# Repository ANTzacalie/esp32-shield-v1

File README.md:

# ESP32 Shield V1

---

## About the Project

- Shield V1 is spacious development shield designed to make working with ESP32 reliable, practical, and accessible. Whether you're prototyping, learning, or building something more permanent, this board gives you the room and connectivity to do it right.

The ESP32 Shield V1 breaks out **all useful GPIO pins** (bootstrapping pins like GPIO11 excluded) through both **terminal block connectors** for permanent wiring and **male pin headers** for Dupont jumper wire access. It supports both the **ESP32 DevKit C** and **ESP32-S** variants — both fit into the onboard 2×19 socket pins.

Power is supplied through a modern **USB-C 6-pin connector**, compatible with any USB-C charger or USB-A to USB-C adapter — no more bulky legacy connectors. A **power LED** confirms the board is live at a glance.

---

## Features

    -  **USB-C Power Input** — 6-pin USB-C connector; works with any USB-C or USB-A (female-to-USB-C) charger
    -  **Full GPIO Breakout** — all useful ESP32 GPIO pins exposed (bootstrapping pins excluded)
    -  **Terminal Block Connectors** — for all useful pins, ideal for permanent or semi-permanent wiring
    -  **Male Pin Headers** — Dupont-compatible, for quick breadboard or jumper wire access
    -  **ESP32 DevKit C & 32S Compatible** — both modules fit the 2×19 socket pin layout
    -  **5V Rail up to 1A** — 2 terminal blocks with 5V and GND in 1:1 configuration
    -  **5V & 3.3V Header Pins** — 2×4 header for 5V and 3.3V (max 500mA via AMS1117-3.3 regulator)
    -  **4×4 GND Header** — dedicated ground header block
    -  **Power Indicator LED** — shows board is powered and ready
    -  **Big, Spacious Board** — generous layout for comfortable hand soldering and clear wiring

---

## Gallery

<p align="center">
  
  &nbsp;&nbsp;
  
</p>

---

## Documents

| Document | Link |
|---|---|
| PCB Layout | [shield_v1_pcb.pdf](esp32_development_shield_v1/auxiliar/screenshots/shield_v1_pcb.pdf) |
| Schematic | [shield_v1_schematic.pdf](esp32_development_shield_v1/auxiliar/screenshots/shield_v1_schematic.pdf) |

---

## Demo

https://github.com/user-attachments/assets/38adf7bb-4b09-42fa-a934-d43c7a3f349f

---

## Folder Structure

```
esp32-shield-v1/
│
├── auxiliar/
│   ├── compatibility_info/       # Compatibility notes for ESP32 variants
│   ├── screenshots/              # Board photos (photo1–photo4)
│   └── test_video/               # Demo video (video.gif / video.mp4)
│
├── pcb/
│   ├── bom_files/                # 📋 Bill of Materials (BOM)
│   ├── drill_files/              # 🔩 Drill files for PCB fabrication
│   └── gerber_files/             # 📦 Gerber files — send these to your PCB fab
│
└── schematic/
    ├── esp32_node_devkit_shield_v1/   # Main schematic project files
    └── symbols&footprints/            # Custom KiCad symbols and footprints
```

> **PCB fabrication files are located in `/pcb/`:**
> - **`/pcb/gerber_files/`** — Production-ready Gerber files for your PCB manufacturer
> - **`/pcb/drill_files/`** — Drill/Excellon files for hole placement
> - **`/pcb/bom_files/`** — Bill of Materials for component sourcing

---

## Getting Started

1. Clone or download this repository
2. Open the schematic in **KiCad** from `/schematic/esp32_node_devkit_shield_v1/`
3. Review the BOM in `/pcb/bom_files/` and source your components
4. Send the files from `/pcb/gerber_files/` and `/pcb/drill_files/` to your preferred PCB manufacturer
5. Assemble, plug in your ESP32 DevKit C or 32S, connect USB-C power, and build something!

---

## Compatibility

| Module | Fits? |
|---|---|
| ESP32 DevKit C | ✅ Yes |
| ESP32-S (DevKitS) | ✅ Yes |

See `/auxiliar/compatibility_info/` for detailed notes.

---

## Power Specifications

| Rail | Max Current | Connector Type |
|---|---|---|
| 5V | 1A | 2× Terminal Block (5V + GND) |
| 5V | — | 2×4 Pin Header |
| 3.3V | 500mA | 2×4 Pin Header (AMS1117-3.3) |
| GND | — | 4×4 Pin Header |

---

## License

This project is open source. Feel free to use, modify, and build upon it for personal and educational purposes.

---

*Made with monster-energy and a soldering iron — student electronics project*

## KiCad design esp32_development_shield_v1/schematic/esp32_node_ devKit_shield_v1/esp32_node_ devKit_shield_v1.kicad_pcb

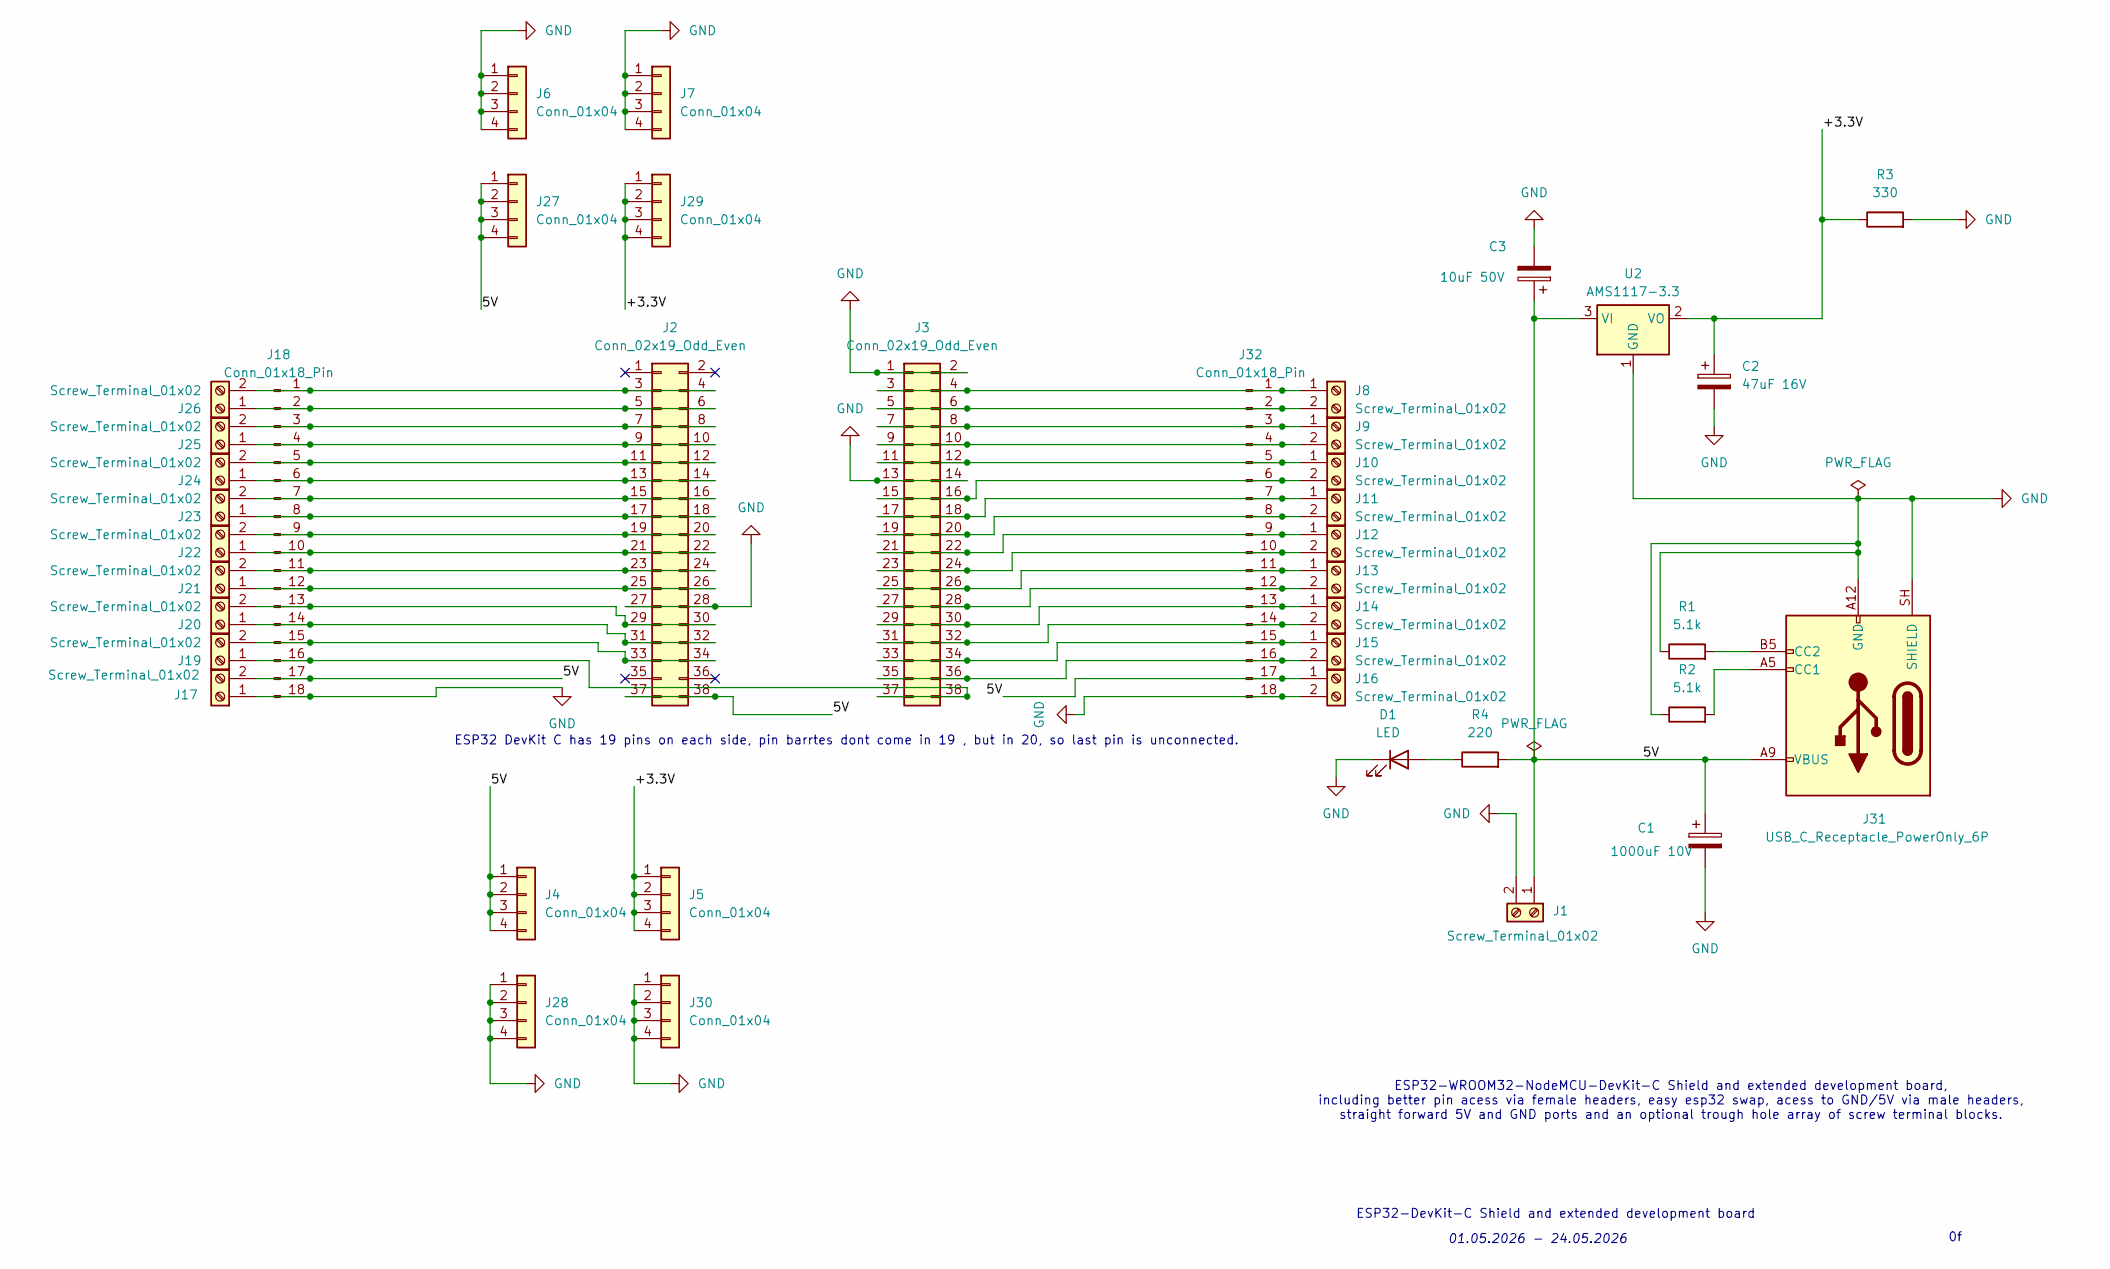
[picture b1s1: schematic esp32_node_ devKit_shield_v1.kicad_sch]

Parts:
C1: 1000uF 10V; CP_Radial_D10.0mm_P5.00mm
C2: 47uF 16V; CP_Radial_D8.0mm_P5.00mm
C3: 10uF 50V; CP_Radial_D8.0mm_P5.00mm
D1: LED; LED_Rectangular_W3.0mm_H2.0mm
J1, J8, J9, J10, J11, J12, J13, J14, J15, J16, J17, J19, J20, J21, J22, J23, J24, J25, J26: Screw_Terminal_01x02; TerminalBlock_RND_205-00232_1x02_P5.08mm_Horizontal
J2, J3: Conn_02x19_Odd_Even; PinSocket_2x19_P2.54mm_Vertical
J4, J5, J6, J7, J27, J28, J29, J30: Conn_01x04; PinHeader_1x04_P2.54mm_Vertical
J18, J32: Conn_01x18_Pin; PinHeader_1x18_P2.54mm_Vertical
J31: USB_C_Receptacle_PowerOnly_6P; USB_C_Receptacle_GCT_USB4125-xx-x_6P_TopMnt_Horizontal
R1, R2: 5.1k; R_Axial_DIN0207_L6.3mm_D2.5mm_P10.16mm_Horizontal
R3: 330; R_Axial_DIN0207_L6.3mm_D2.5mm_P10.16mm_Horizontal
R4: 220; R_Axial_DIN0207_L6.3mm_D2.5mm_P10.16mm_Horizontal
U2: AMS1117-3.3; SOT-223-3_TabPin2

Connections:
/5V: C1.1, C3.1, J1.1, J2.37, J2.38, J4.1, J4.2, J4.3, J4.4, J16.1, J17.2, J18.17, J27.1, J27.2, J27.3, J27.4, J31.A9 (VBUS), J31.B9 (VBUS), J32.17, R4.2, U2.3 (VI)
/+3.3V: C2.1, J5.1, J5.2, J5.3, J5.4, J29.1, J29.2, J29.3, J29.4, R3.1, U2.2 (VO)
GND: C1.2, C2.2, C3.2, D1.1 (K), J1.2, J2.27, J2.28, J3.1, J3.2, J3.13, J3.14, J6.1, J6.2, J6.3, J6.4, J7.1, J7.2, J7.3, J7.4, J16.2, J17.1, J18.18, J28.1, J28.2, J28.3, J28.4, J30.1, J30.2, J30.3, J30.4, J31.A12 (GND), J31.B12 (GND), J31.SH (SHIELD), J32.18, R1.1, R2.1, R3.2, U2.1 (GND)
unnamed: D1.2 (A), R4.1
unnamed: J3.3, J3.4, J8.1, J32.1
unnamed: J3.5, J3.6, J8.2, J32.2
unnamed: J3.7, J3.8, J9.1, J32.3
unnamed: J3.9, J3.10, J9.2, J32.4
unnamed: J3.11, J3.12, J10.1, J32.5
unnamed: J3.15, J3.16, J10.2, J32.6
unnamed: J3.17, J3.18, J11.1, J32.7
unnamed: J3.19, J3.20, J11.2, J32.8
unnamed: J3.21, J3.22, J12.1, J32.9
unnamed: J3.23, J3.24, J12.2, J32.10
unnamed: J3.25, J3.26, J13.1, J32.11
unnamed: J3.27, J3.28, J13.2, J32.12
unnamed: J3.29, J3.30, J14.1, J32.13
unnamed: J3.31, J3.32, J14.2, J32.14
unnamed: J3.33, J3.34, J15.1, J32.15
unnamed: J3.35, J3.36, J15.2, J32.16
unnamed: J2.3, J2.4, J18.1, J26.2
unnamed: J2.5, J2.6, J18.2, J26.1
unnamed: J2.7, J2.8, J18.3, J25.2
unnamed: J2.9, J2.10, J18.4, J25.1
unnamed: J2.11, J2.12, J18.5, J24.2
unnamed: J2.13, J2.14, J18.6, J24.1
unnamed: J2.15, J2.16, J18.7, J23.2
unnamed: J2.17, J2.18, J18.8, J23.1
unnamed: J2.19, J2.20, J18.9, J22.2
unnamed: J2.21, J2.22, J18.10, J22.1
unnamed: J2.23, J2.24, J18.11, J21.2
unnamed: J2.25, J2.26, J18.12, J21.1
unnamed: J2.29, J2.30, J18.13, J20.2
unnamed: J2.31, J2.32, J18.14, J20.1
unnamed: J2.33, J2.34, J18.15, J19.2
unnamed: J3.37, J3.38, J18.16, J19.1
unnamed: J31.A5 (CC1), R2.2
unnamed: J31.B5 (CC2), R1.2

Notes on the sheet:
ESP32-DevKit-C Shield and extended development board
ESP32-WROOM32-NodeMCU-DevKit-C Shield and extended development board, including better pin acess via female headers, easy esp32 swap, acess to GND/5V via male headers, straight forward 5V and GND ports and an optional trough hole array of screw terminal blocks.
ESP32 DevKit C has 19 pins on each side, pin barrtes dont come in 19 , but in 20, so last pin is unconnected.
01.05.2026 - 24.05.2026

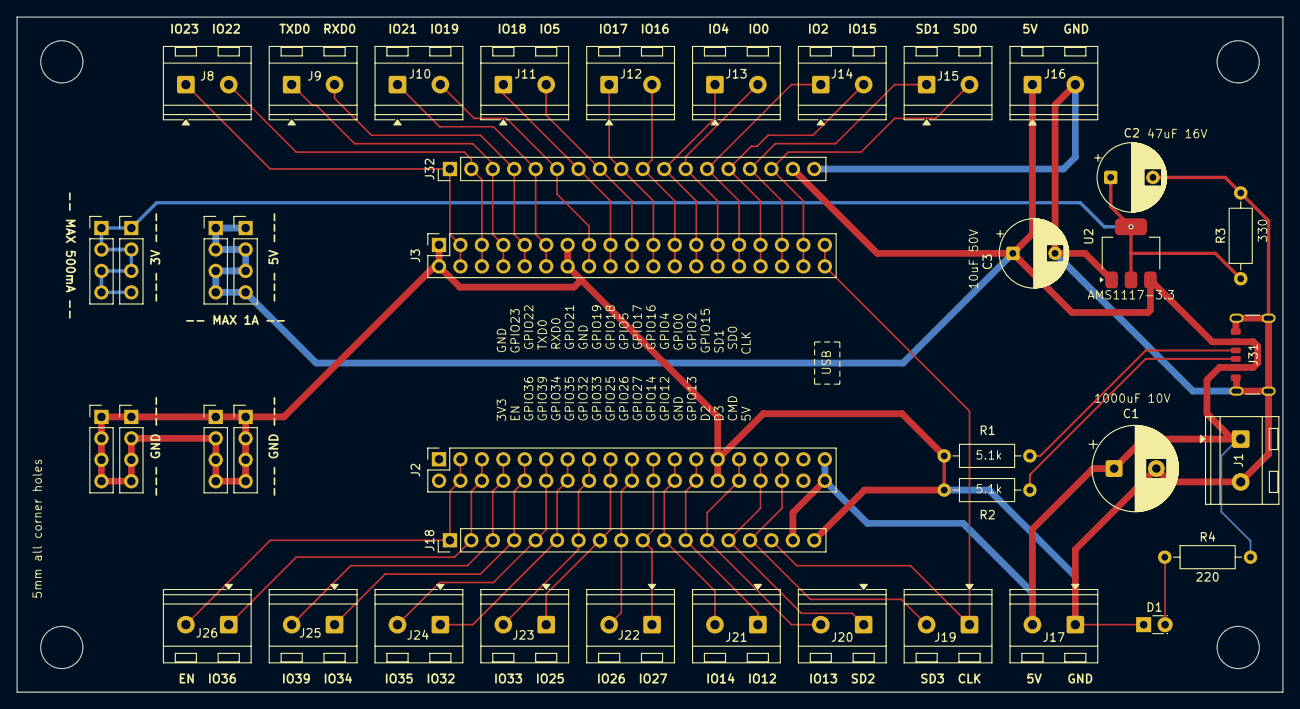
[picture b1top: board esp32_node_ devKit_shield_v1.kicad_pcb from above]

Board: 2 copper layers, 150.0 x 80.0 mm, 41 parts (0 on the bottom side), 38 nets.

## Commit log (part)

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2026-05-10 ESP32 Devkit Shield V1 finished
    - ESP32 Shield V1 scheme finished.
    - Capacitors for AMS1117 3.3 set.
    - Circuit 1000uF Capacitors used to cover the ESP32 Devkit that requires 550uF, and all other components that are gonna be conected to the 5V and 3.3V pins.
    - Shield PCB completed and inspected, ready for fabrication.
2026-05-10 folder structure changed
2026-05-13 *
    Replaced socket with header
2026-05-14 Added LED for power on/off
2026-05-14 *removed backup files
2026-05-14 added components used readme
2026-05-15 Fix compatibility info formatting and spelling
    Corrected spelling of 'following' and adjusted formatting for clarity.
2026-05-15 Update section title from 'Components Used' to 'Components'
2026-05-15 Add README for ESP32 Shield V1 project
    This README provides detailed information about the ESP32 Shield V1 project, including features, gallery, demo, folder structure, getting started instructions, compatibility, power specifications, an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
2026-05-15 Update image link for Photo 1 in README
2026-05-15 Fix image path in README.md
2026-05-15 Fix image path for Photo 1 in README.md
2026-05-15 Refactor gallery images to HTML format
    Updated the gallery section to use HTML for image alignment and added a new image.
2026-05-15 Remove duplicate feature descriptions in README
2026-05-23 PCB.zip files uploaded
    2-5 days until PCB are received
